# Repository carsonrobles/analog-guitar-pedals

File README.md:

# guitar-pedals
Collection of homemade guitar pedals.

Current pedals:
- fuzz face

Future additions:
- wah wah
- some other form of distortion (i.e. overdrive)
- simple buffer circuit to place between pedals

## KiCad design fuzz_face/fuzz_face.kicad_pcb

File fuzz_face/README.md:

# Fuzz Face
Fuzz pedal featuring volume and fuzz controls strongly inspired by the classic Fuzz Face pedal.

### Schematic

### Layout

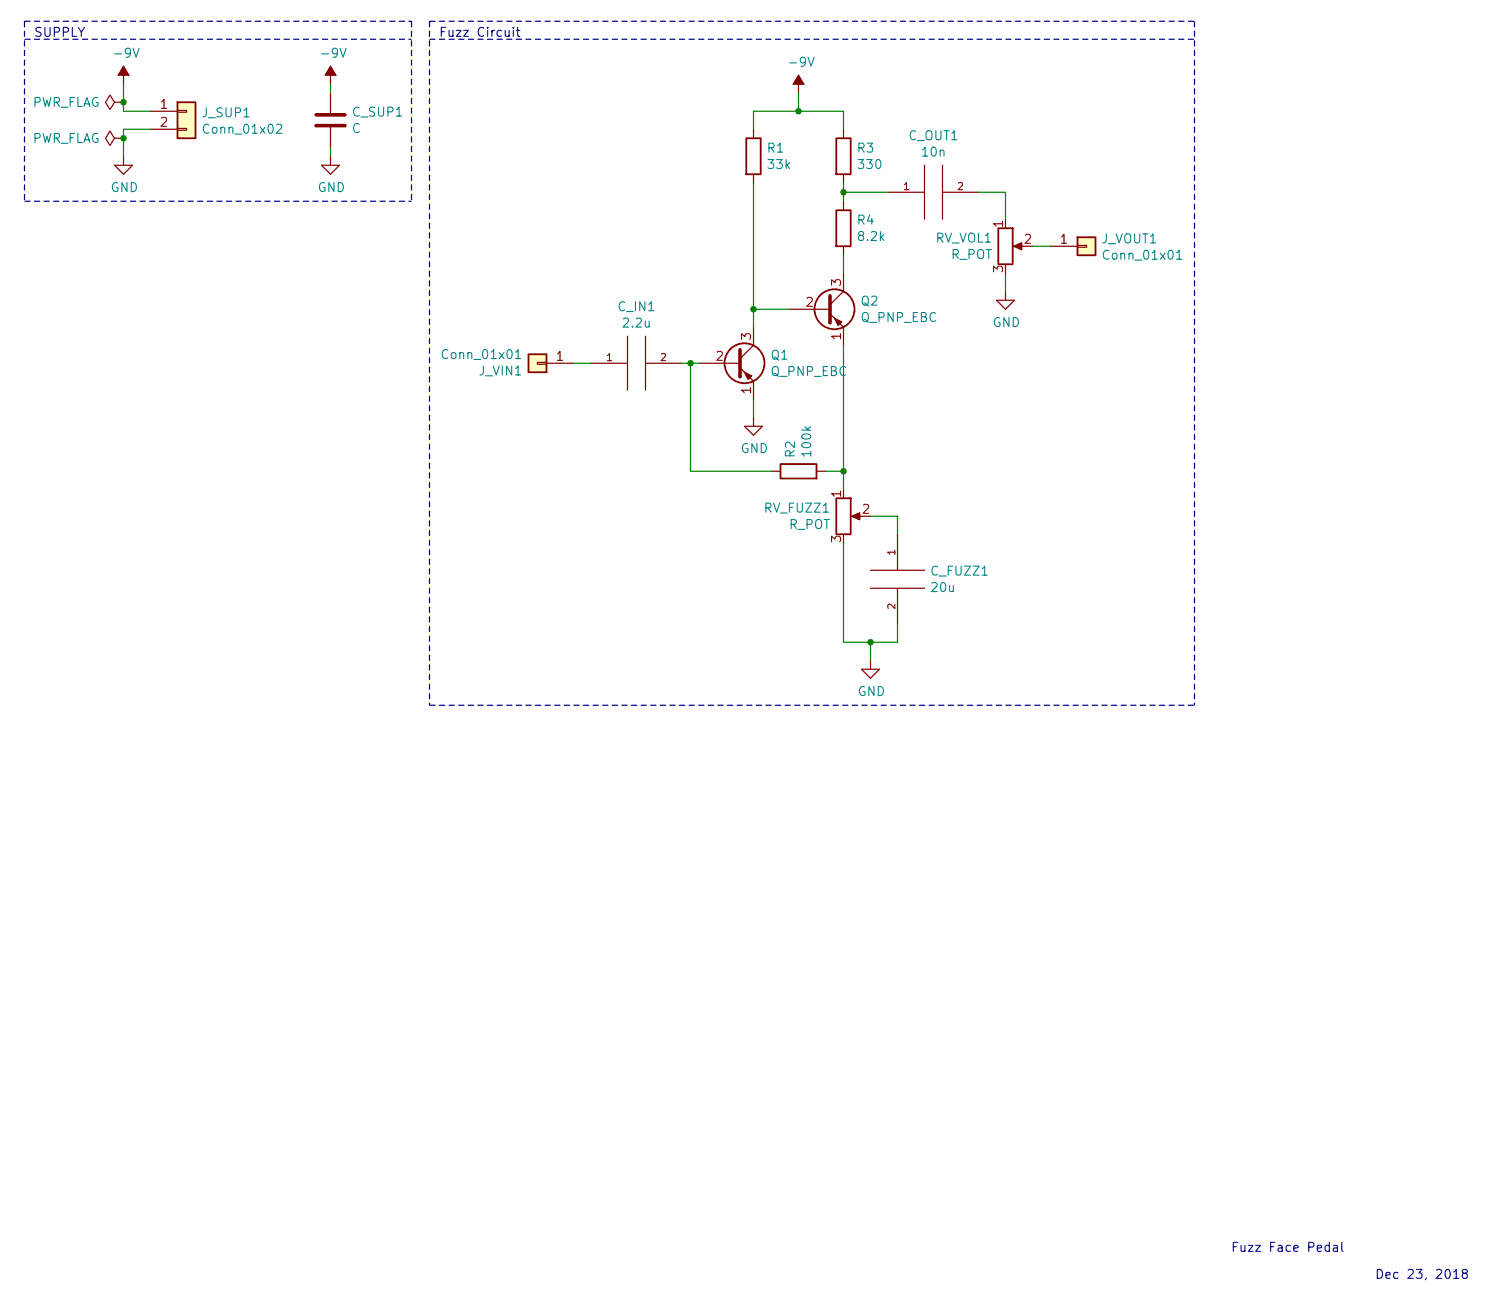
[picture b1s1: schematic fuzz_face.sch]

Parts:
C_FUZZ1: 20u; C_Disc_D9.0mm_W5.0mm_P10.00mm
C_IN1: 2.2u; C_Disc_D9.0mm_W5.0mm_P10.00mm
C_OUT1: 10n; C_Disc_D9.0mm_W5.0mm_P10.00mm
C_SUP1: C; C_Disc_D9.0mm_W5.0mm_P10.00mm
J_SUP1: Conn_01x02; SolderWirePad_1x02_P7.62mm_Drill2mm
J_VIN1: Conn_01x01; SolderWirePad_1x01_Drill2mm
J_VOUT1: Conn_01x01; SolderWirePad_1x01_Drill2mm
Q1, Q2: Q_PNP_EBC; TO-220-3_Vertical
R1: 33k; R_Box_L13.0mm_W4.0mm_P9.00mm
R2: 100k; R_Box_L13.0mm_W4.0mm_P9.00mm
R3: 330; R_Box_L13.0mm_W4.0mm_P9.00mm
R4: 8.2k; R_Box_L13.0mm_W4.0mm_P9.00mm
RV_FUZZ1: R_POT; TerminalBlock_bornier-3_P5.08mm
RV_VOL1: R_POT; TerminalBlock_bornier-3_P5.08mm

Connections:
-9V: C_SUP1.1, J_SUP1.1, R1.1, R3.1
GND: C_FUZZ1.2, C_SUP1.2, J_SUP1.2, Q1.1 (E), RV_FUZZ1.3, RV_VOL1.3
unnamed: C_FUZZ1.1, RV_FUZZ1.2
unnamed: C_IN1.1, J_VIN1.1
unnamed: C_IN1.2, Q1.2 (B), R2.1
unnamed: C_OUT1.1, R3.2, R4.1
unnamed: C_OUT1.2, RV_VOL1.1
unnamed: J_VOUT1.1, RV_VOL1.2
unnamed: Q1.3 (C), Q2.2 (B), R1.2
unnamed: Q2.1 (E), R2.2, RV_FUZZ1.1
unnamed: Q2.3 (C), R4.2

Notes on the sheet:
Fuzz Face Pedal
Dec 23, 2018
SUPPLY
Fuzz Circuit

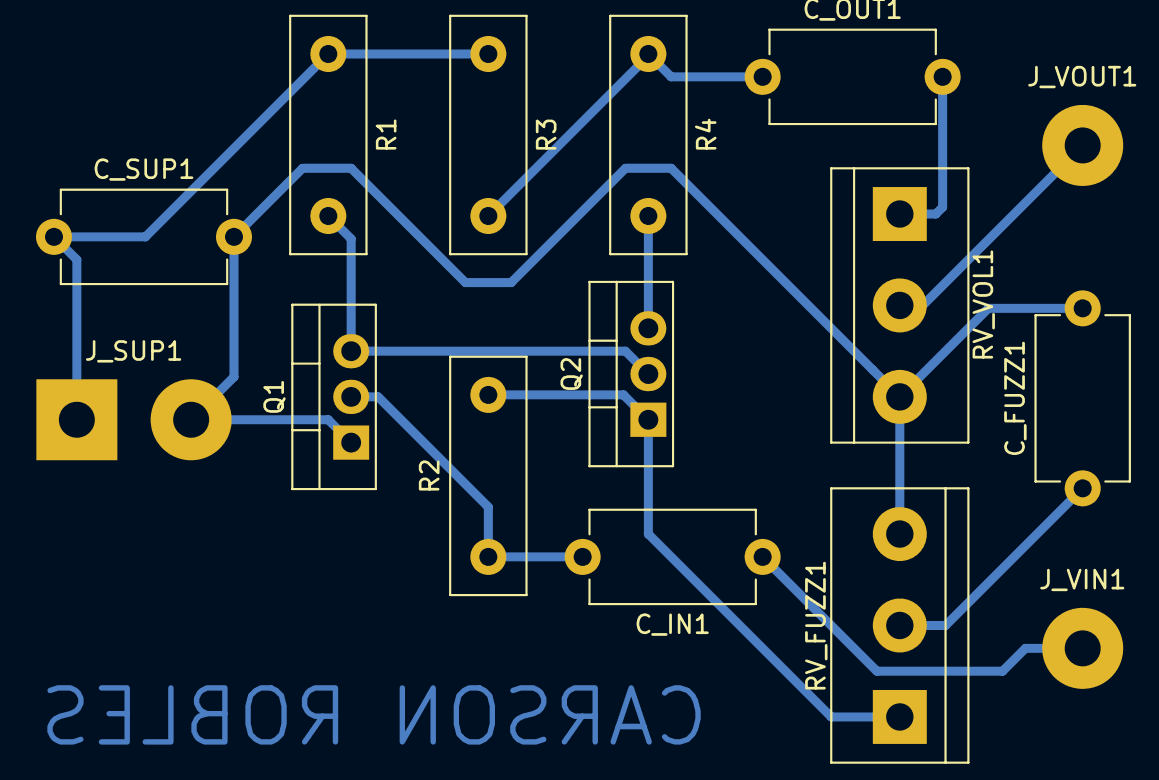
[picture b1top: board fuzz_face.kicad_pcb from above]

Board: 2 copper layers, 15 parts (0 on the bottom side), 11 nets.

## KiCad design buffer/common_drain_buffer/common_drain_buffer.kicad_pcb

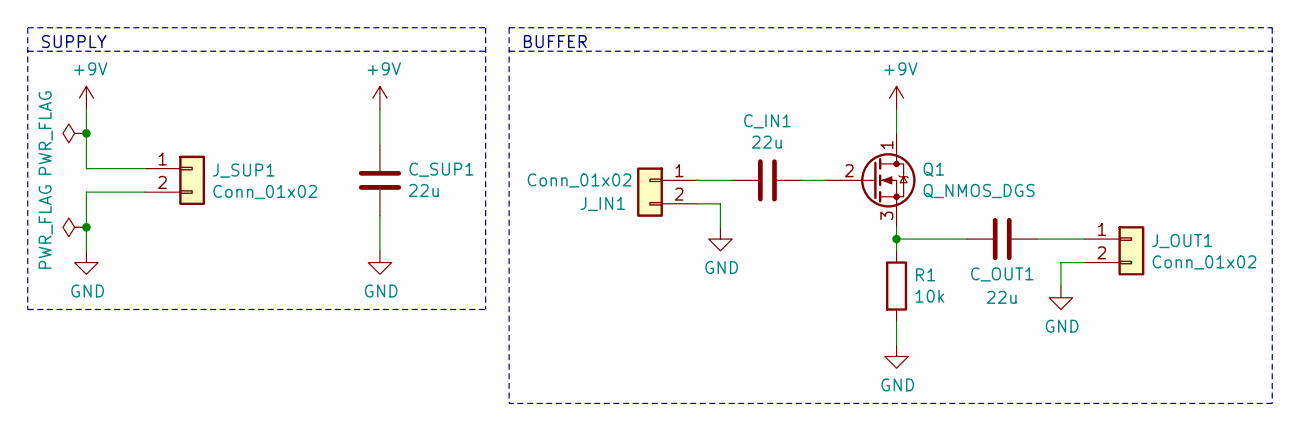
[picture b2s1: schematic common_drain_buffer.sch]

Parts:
C_IN1: 22u
C_OUT1: 22u
C_SUP1: 22u
J_IN1: Conn_01x02
J_OUT1: Conn_01x02
J_SUP1: Conn_01x02
Q1: Q_NMOS_DGS
R1: 10k

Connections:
+9V: C_SUP1.1, J_SUP1.1, Q1.1 (D)
GND: C_SUP1.2, J_IN1.2, J_OUT1.2, J_SUP1.2, R1.2
unnamed: C_IN1.1, Q1.2 (G)
unnamed: C_IN1.2, J_IN1.1
unnamed: C_OUT1.1, Q1.3 (S), R1.1
unnamed: C_OUT1.2, J_OUT1.1

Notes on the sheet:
SUPPLY
BUFFER

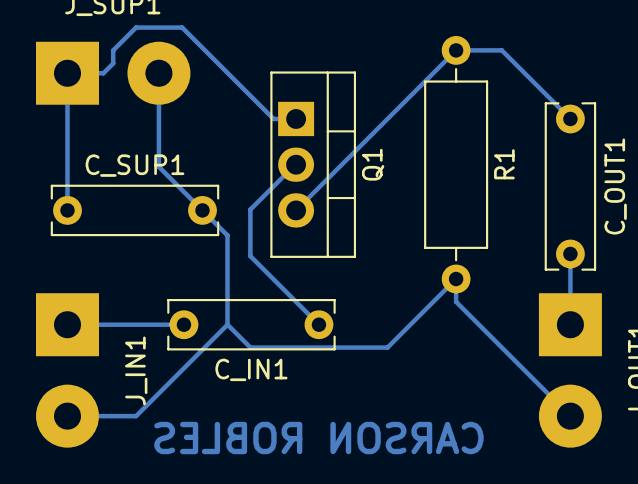
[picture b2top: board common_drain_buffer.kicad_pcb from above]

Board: 2 copper layers, 8 parts (0 on the bottom side), 6 nets.

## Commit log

2019-01-02 Add fuzz pedal.
2019-01-02 Add gitignore and images of fuzz schematic and layout.
2019-01-02 Update fuzz README.
2019-01-03 Add simple common drain buffer.
